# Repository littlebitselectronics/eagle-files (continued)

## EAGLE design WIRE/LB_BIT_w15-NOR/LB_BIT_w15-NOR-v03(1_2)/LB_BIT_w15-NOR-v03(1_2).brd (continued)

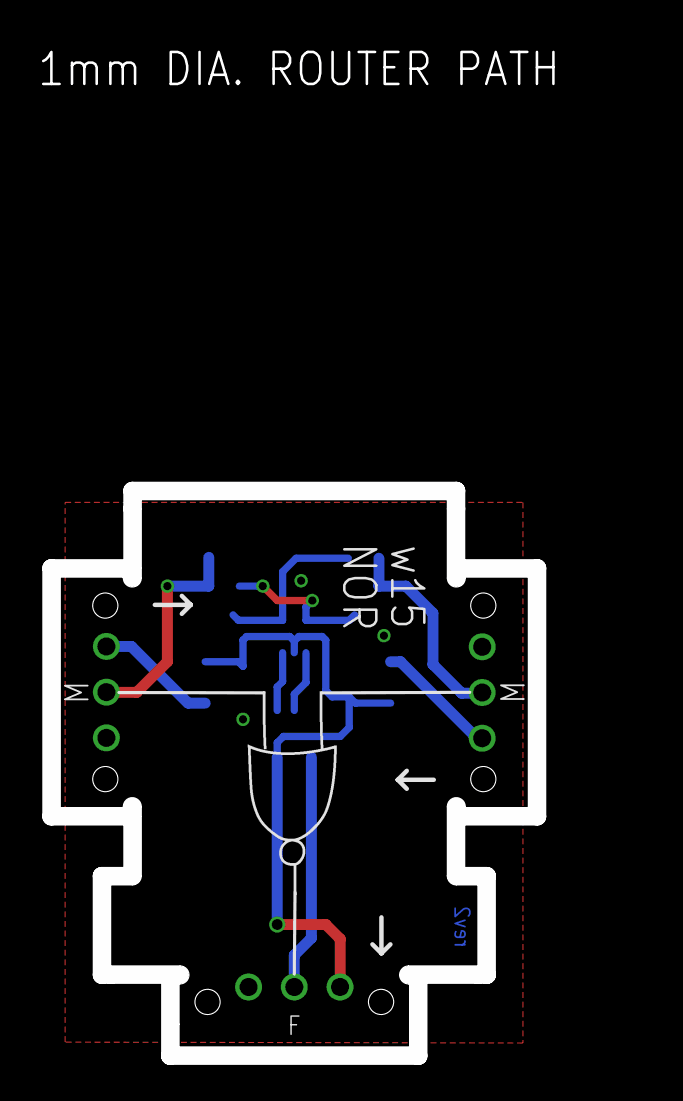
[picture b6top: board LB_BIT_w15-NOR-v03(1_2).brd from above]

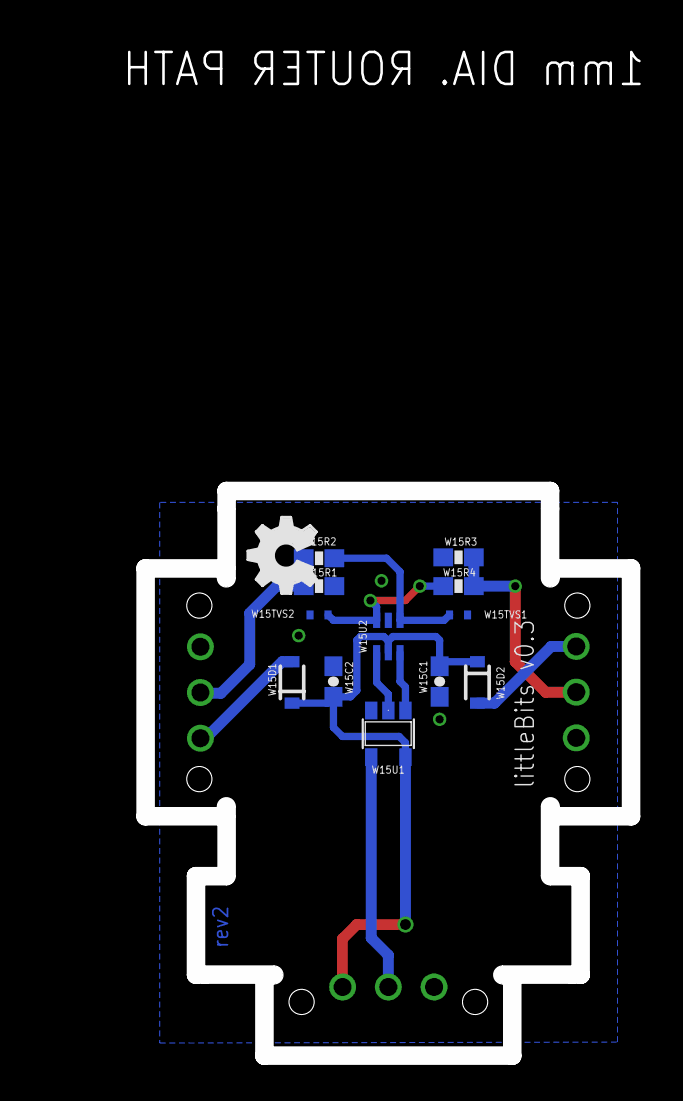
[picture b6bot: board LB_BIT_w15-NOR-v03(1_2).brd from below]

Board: 2 copper layers, 27.0 x 31.4 mm, 20 parts (12 on the bottom side), 11 nets.

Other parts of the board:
U$4: NOR_IMAGE
U$6: OSHW_FILLX150_NOTEXT

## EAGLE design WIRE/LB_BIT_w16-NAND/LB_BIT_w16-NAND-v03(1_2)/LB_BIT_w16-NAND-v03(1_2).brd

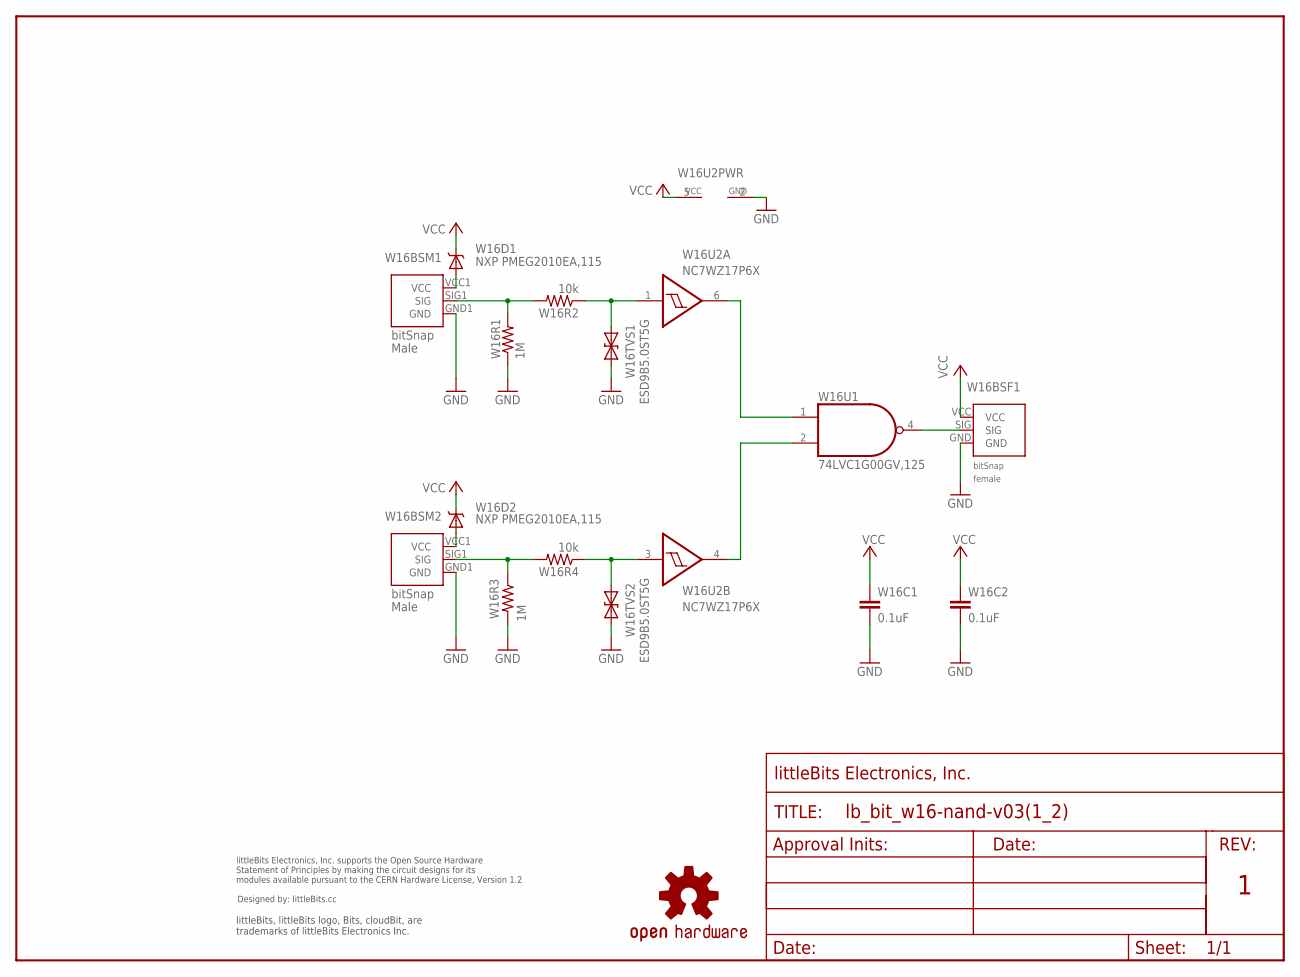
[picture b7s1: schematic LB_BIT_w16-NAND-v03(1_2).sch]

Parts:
U$1: OSHWCREDIT
U$2: OSHW-LOGOL; OSHW-LOGO-L
U$7: FRAME-LETTER-OHWOHW; FABDWG01-OHW
W16BSF1: BITSNAP_V03_FEMALE
W16BSM1, W16BSM2: BITSNAP_V03_MALE
W16C1, W16C2: 0.1uF; CAP-0603
W16D1, W16D2: NXP PMEG2010EA,115; SOD-323
W16R1, W16R3: 1M; 0603-RES
W16R2, W16R4: 10k; 0603-RES
W16TVS1, W16TVS2: ESD9B5.0ST5G; SOD-923
W16U1: 74LVC1G00GV,125; SOT23-5
W16U2: NC7WZ17P6X; SC70-6

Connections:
GND: W16BSF1.GND, W16BSM1.GND1 (GND), W16BSM2.GND1 (GND), W16C1.2, W16C2.2, W16R1.1, W16R3.2, W16TVS1.1 (A), W16TVS2.1 (A), W16U1.3 (GND), W16U2.2 (GND)
unnamed: W16BSM2.SIG1 (SIG), W16R3.1, W16R4.2
unnamed: W16U1.1 (I0), W16U2.6 (O)
unnamed: W16BSM1.VCC1 (VCC), W16D1.2 (A)
unnamed: W16U1.2 (I1), W16U2.4 (O)
unnamed: W16BSM2.VCC1 (VCC), W16D2.2 (A)
unnamed: W16BSM1.SIG1 (SIG), W16R1.2, W16R2.2
unnamed: W16R2.1, W16TVS1.2 (C), W16U2.1 (I)
unnamed: W16R4.1, W16TVS2.2 (C), W16U2.3 (I)
unnamed: W16BSF1.SIG, W16U1.4 (O)
VCC: W16BSF1.VCC, W16C1.1, W16C2.1, W16D1.1 (C), W16D2.1 (C), W16U1.5 (VCC), W16U2.5 (VCC)

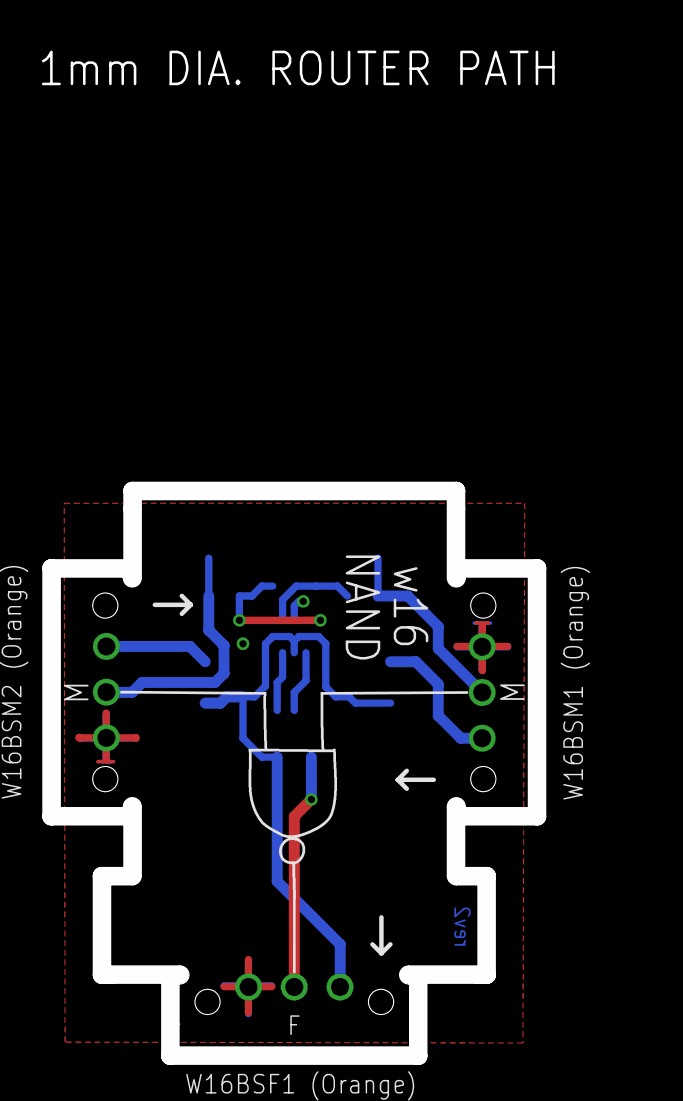
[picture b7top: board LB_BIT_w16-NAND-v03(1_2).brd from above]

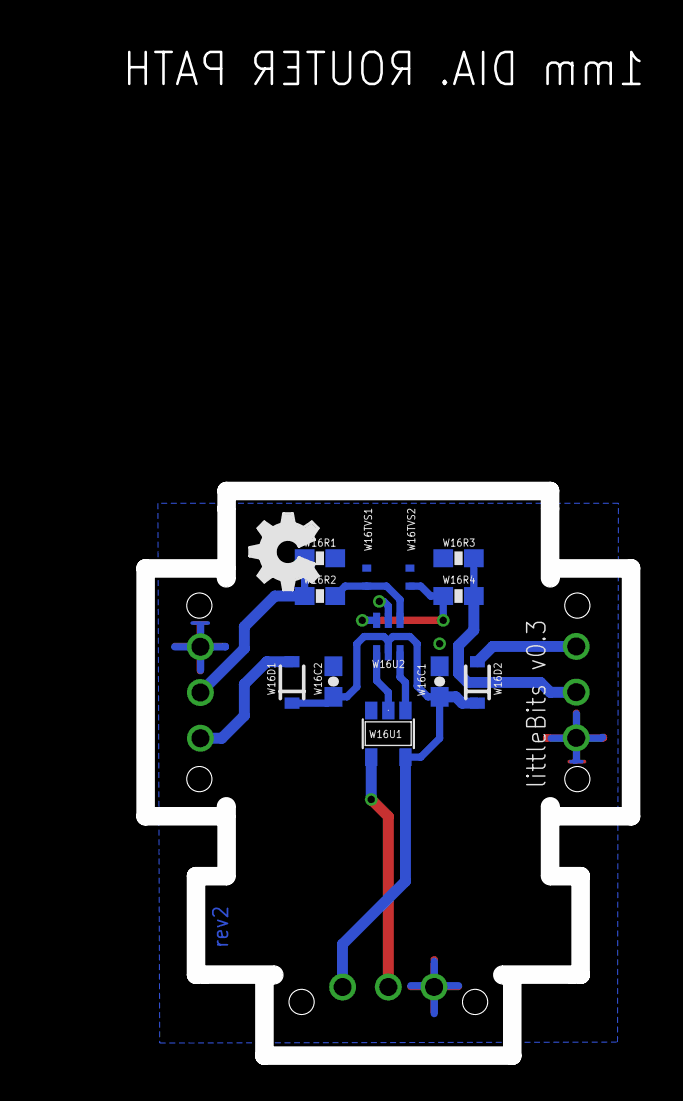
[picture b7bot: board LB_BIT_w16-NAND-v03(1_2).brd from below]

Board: 2 copper layers, 27.0 x 31.4 mm, 20 parts (12 on the bottom side), 11 nets.

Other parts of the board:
U$4: NAND_IMAGE
U$6: OSHW_FILLX150_NOTEXT

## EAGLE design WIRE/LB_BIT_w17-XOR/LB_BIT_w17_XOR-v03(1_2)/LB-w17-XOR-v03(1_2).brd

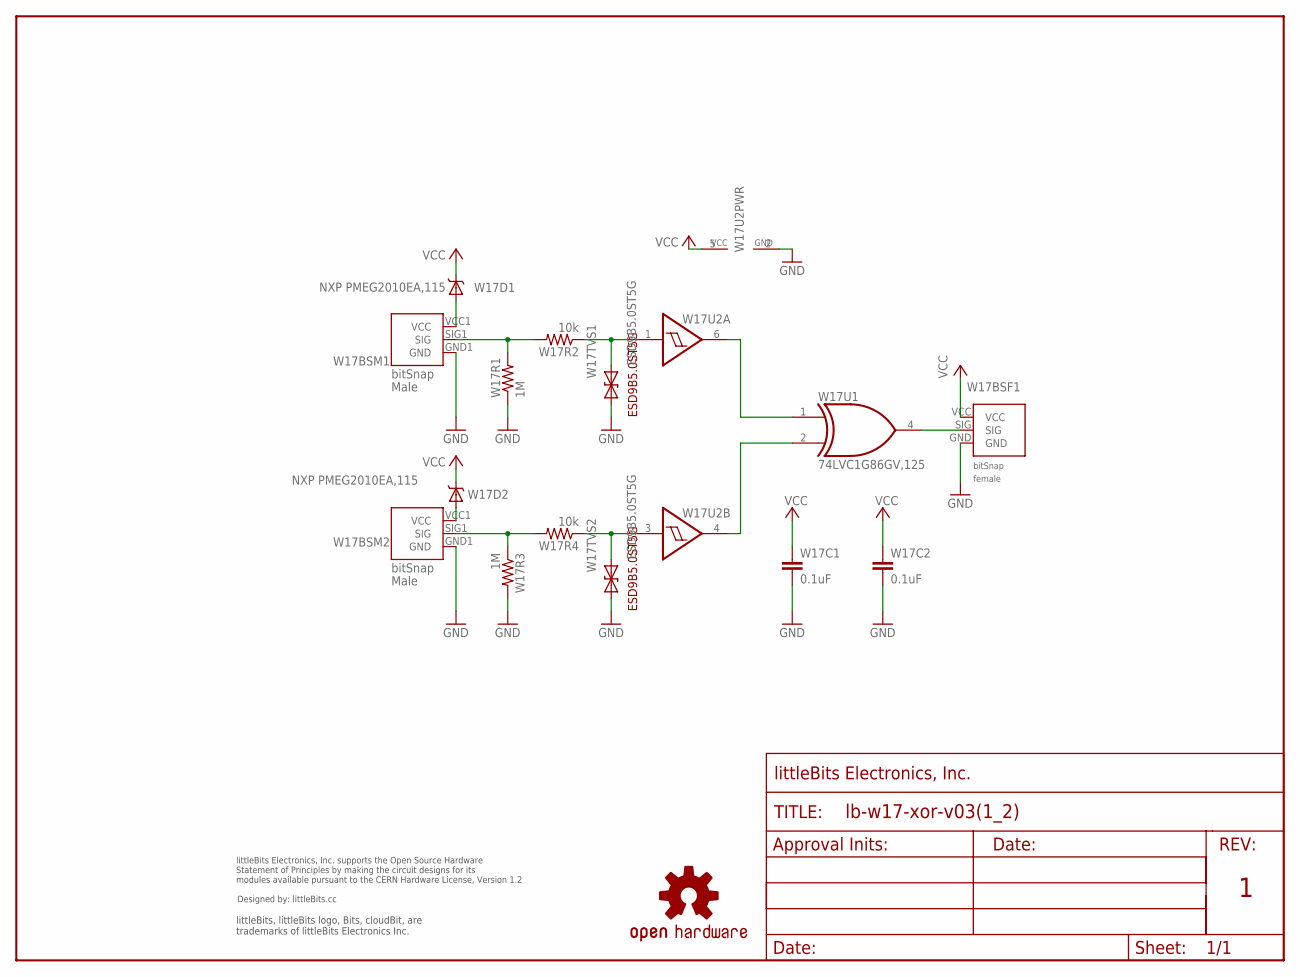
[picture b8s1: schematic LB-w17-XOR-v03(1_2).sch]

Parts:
U$1: FRAME-LETTER-OHWOHW; FABDWG01-OHW
U$2: OSHW-LOGOL; OSHW-LOGO-L
U$5: OSHWCREDIT
W17BSF1: BITSNAP_V03_FEMALE
W17BSM1, W17BSM2: BITSNAP_V03_MALE
W17C1, W17C2: 0.1uF; CAP-0603
W17D1, W17D2: NXP PMEG2010EA,115; SOD-323
W17R1, W17R3: 1M; 0603-RES
W17R2, W17R4: 10k; 0603-RES
W17TVS1, W17TVS2: ESD9B5.0ST5G; SOD-923
W17U1: 74LVC1G86GV,125; SOT23-5
W17U2: NC7WZ17P6X; SC70-6

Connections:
GND: W17BSF1.GND, W17BSM1.GND1 (GND), W17BSM2.GND1 (GND), W17C1.2, W17C2.2, W17R1.1, W17R3.2, W17TVS1.1 (A), W17TVS2.1 (A), W17U1.3 (GND), W17U2.2 (GND)
unnamed: W17BSM2.SIG1 (SIG), W17R3.1, W17R4.2
unnamed: W17U1.1 (I0), W17U2.6 (O)
unnamed: W17BSM1.VCC1 (VCC), W17D1.2 (A)
unnamed: W17U1.2 (I1), W17U2.4 (O)
unnamed: W17BSM2.VCC1 (VCC), W17D2.2 (A)
unnamed: W17BSM1.SIG1 (SIG), W17R1.2, W17R2.2
unnamed: W17R2.1, W17TVS1.2 (C), W17U2.1 (I)
unnamed: W17R4.1, W17TVS2.2 (C), W17U2.3 (I)
unnamed: W17BSF1.SIG, W17U1.4 (O)
VCC: W17BSF1.VCC, W17C1.1, W17C2.1, W17D1.1 (C), W17D2.1 (C), W17U1.5 (VCC), W17U2.5 (VCC)

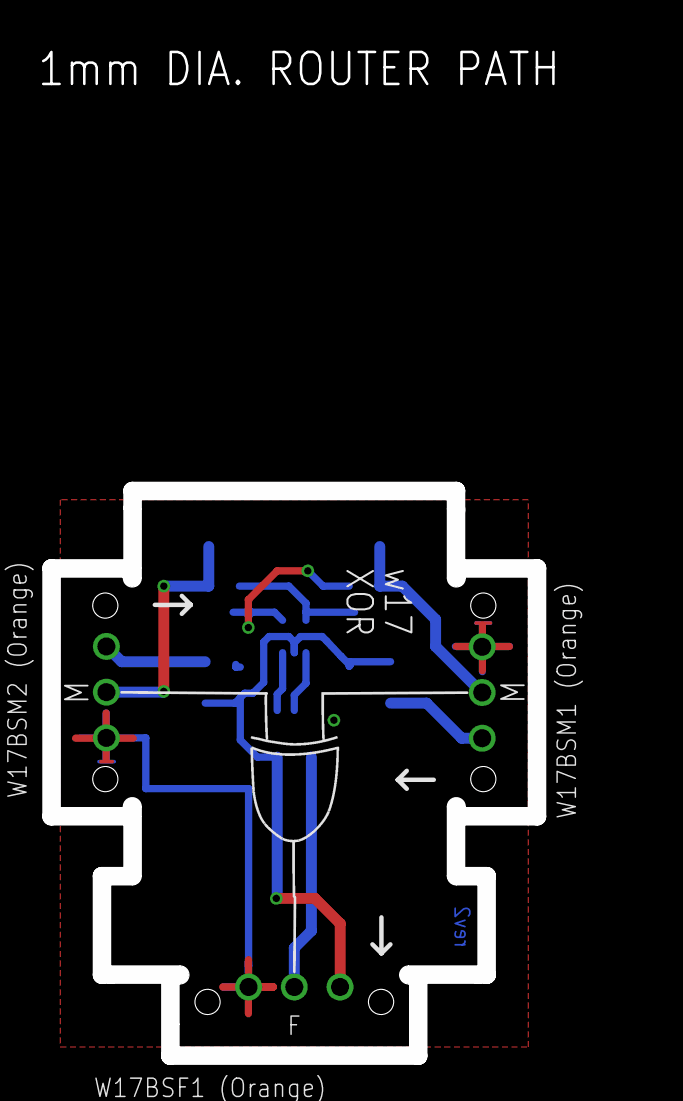
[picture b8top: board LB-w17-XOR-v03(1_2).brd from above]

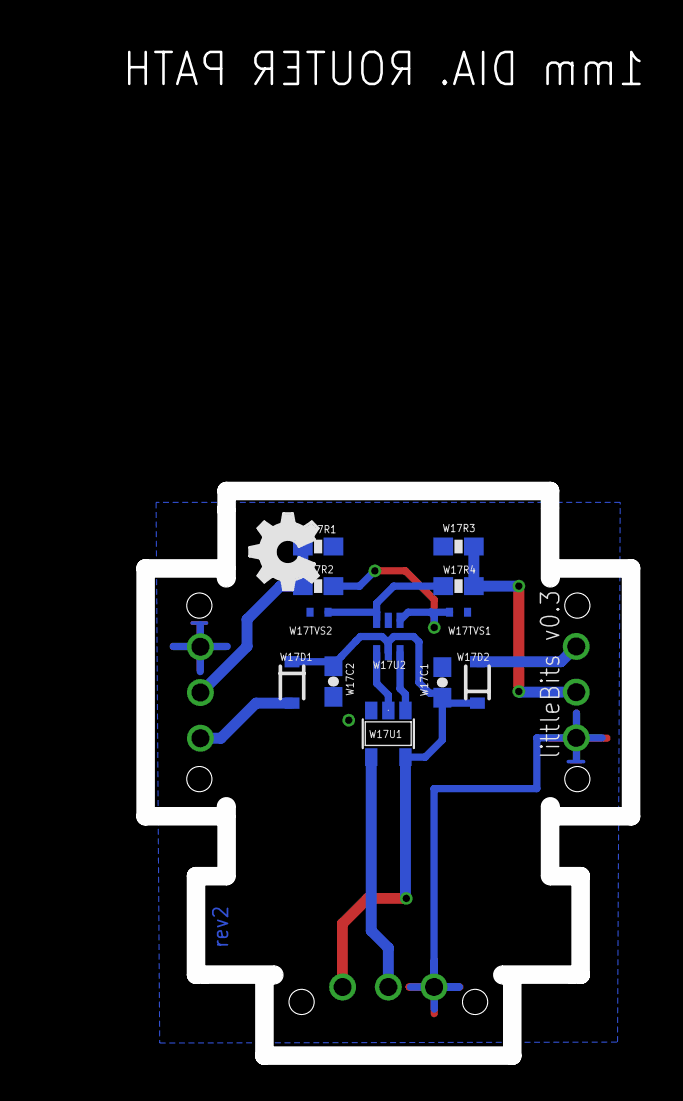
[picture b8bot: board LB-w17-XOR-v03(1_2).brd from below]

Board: 2 copper layers, 27.0 x 31.4 mm, 20 parts (12 on the bottom side), 11 nets.

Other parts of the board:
U$4: XOR_IMAGE
U$6: OSHW_FILLX150_NOTEXT
